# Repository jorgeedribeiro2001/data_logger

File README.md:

# Data Logger Project

## Overview
This repository contains the implementation of a data logger project designed for real-time and remote data acquisition during the shipment of products. The project includes scripts for data processing, device software, and a web interface for data visualization and control.

## Repository Structure

- **Back-End Scripts**: Scripts for data processing and storage.
- **Device Software (Microcontroller)**: Code for the microcontroller used in the data logging device.
- **Django Web-Framework**: Web application framework for interfacing with the data logger.
- **Tests and Results**: Testing scripts and result logs.
- **PCB Project**: KiCad Project of the PCB for the prototype.

## Description of the Implemented Solution

The data logger system uses the ESP32-E Firebeetle 2 microcontroller as the main unit. It works with several sensors to meet the project's requirements:

- **Vibration and Impact Monitoring**: Uses the IAM-20680 accelerometer and gyroscope.
- **Environmental Monitoring**: Uses the BME680 sensor to measure temperature, humidity, and pressure. Both sensors communicate with the microcontroller using the I2C protocol.
- **Data Storage**: Uses a PMod microSD reader module, which communicates via the SPI protocol, for local data storage.
- **Mobile Communication and GPS**: Uses the Ai-Thinker A9G module for mobile network communication and GPS tracking, interfacing via the UART protocol.

Data is sent using the MQTT protocol. Back-end scripts receive this data, convert it to JSON format, and send it to the Django web framework using HTTP Post requests.

##### Django Web Platform

The Django framework manages the data and web platform, providing features such as:

- **Data Storage**: Uses an SQLite database to store user information, trip details, configurations, and data file paths.
- **Interactive Visualization**: Uses JavaScript libraries like Highcharts for graphs and Leaflet for maps to show dynamic data on the trip monitoring page.

## Data Acquisition
A prototype was made with a PCB (KiCad Project), as shown in the next picture. This solution has one I2C connector with a Groove connector for the BME680 sensor. Two more I2C connectors are used, each with a TE Connectivity 1744418-4 connector with a 2.5mm pitch. Two SPI connectors have been added. One is for the microSD module, while the other is for the CS pin linked to GPIO 35 (A3) of the ESP32. The latter connector uses the TE Connectivity 1744418-6 with a 2.5mm pitch. This lets you add or try out other sensors. The design also has extra pins for GND, 3V3, and VCC, as well as two ESP32 serial port pins and extra free GPIOs, all marked on the PCB.

### Microcontroller Program

The microcontroller program is developed using the ESP32 microcontroller and various sensors to monitor parameters such as temperature, humidity, pressure, impacts, vibration, and location. The code is structured into tasks that handle sensor readings, data storage, and communication with the web platform via MQTT.

### Key Components:
- **ESP32 Microcontroller**: Handles sensor integration and data processing.
- **Sensors**: Include BME680 for environmental data, IMU for motion data, and the Ai-Thinker A9G for location tracking and communication.
- **SD Card**: Certain SD cards are occasionally unrecognised by the device. To ascertain the functionality of an SD card, connect the device to a computer and open a serial port. During the initialisation process, the system will indicate whether the SD card is recognisable. If the card is recognised, the available memory will be displayed. ***It is crucial to format the SD card using the FAT32 file system to ensure proper operation.*** Among the tested SD cards, the Kingston CANVAS Select Plus models with capacities of 32GB and 64GB (class 10) have proven to be reliable.

- **SIM Card**: The device is configured to utilise a SIM plan card for communication via a 2G network to access the internet. The SIM operator employed in this instance is Vodafone Portugal, with the Access Point Name (APN) specified as `net2.vodafone.pt`.
   
   ***It is crucial to note that if a different SIM operator is used, it is necessary to modify the APN configuration within the hardware programme to match the new operator's APN. Furthermore, it is imperative to disable the PIN on the SIM card, as the device lacks the capability to handle PIN entry.*** This functionality must be implemented to avoid potential security vulnerabilities.

### Running the Microcontroller Program:
1. **Set Up the Development Environment**:
   - Install the necessary tools and libraries for ESP32 development.
   - Use the Arduino IDE or PlatformIO for code uploading.

2. **Upload the Code**:
   - Connect the ESP32 to your computer.
   - Compile and upload the code from the `microcontroller` directory.

For initial configurations, the device is pre-configured with specific settings, such as a unique identifier, the initial MQTT address and port, and the APN for network connectivity. This can be encounter on the PogV8.ino file.

If you do not wish to use the remote configuration feature, you can manually define each configuration below in the `Definitions of Global Variables of the Program` section. To do this, you will need to set the `remote_configuration` variable to `false`. 

In the case of remote configuration, if a configuration file is present, the system variables are set according to the specifications outlined in the JSON document created in the "Create Trip" webpage. If the internal memory does not contain a configuration file, the A9G module is activated and configured. This module subscribes to the "config" topic on the MQTT broker and awaits the receipt of the JSON file for up to 60 seconds. During this interval, the embedded LED on the microcontroller is programmed to blink at 500 ms intervals. The user must access the Devices Manager webpage and then press the button "Send Configuration."
Upon receipt of a file, the device proceeds to process it and verify whether the JSON file’s device ID matches the ID coded into the device. Each device ID is unique. If the IDs match, the device sets all global variables and copies the JSON file to the internal memory. Once the configuration is complete, the LED remains illuminated for three seconds before turning off. This signifies the setup process is finished and the system is ready for operation.

The end mode, represented in Figure 4.13, is initiated when the user presses the embedded button on the microcontroller for a period of three seconds, thereby initiating the procedure and activating the embedded LED.

## Data Processing and Visualization

The data processing and visualization for the data logger system is managed through a series of scripts and a Django-based web platform. The system architecture and the functions of each script are described below.

### System Architecture

1. **Data Acquisition**:
   - The data logger devices collect data on temperature, humidity, pressure, impacts, vibration, and location.
   - This data is transmitted to the MQTT Broker (Mosquitto) using the MQTT protocol.

2. **Data Processing**:
   - **Script Data Receiver**: Subscribes to the MQTT topics to receive data from the data loggers.
   - **Script Data Processing**: Processes the raw data, converts it into JSON format, and prepares it for storage and visualization.
   - **Script Remote Configuration**: Publishes configuration settings to the data loggers.

3. **Data Storage and Management**:
   - The processed data is stored in an SQLite database, which keeps information about users, trips, trip configurations, and data file paths.
   - Additional processing by **Script Data PSD Processing** converts the raw data for FFT segments into Power Spectral Density (PSD) format for further analysis in the web platform.

4. **Web Framework (Django)**:
   - **Views.py**: Handles HTTP requests and returns responses to the client. It interacts with the models and templates to fetch and display data.
   - **Models.py**: Defines the database schema and interacts with the SQLite database to retrieve and store data.
   - **Urls.py**: Maps URLs to the corresponding views, enabling navigation within the web application.
   - **Templates**: HTML files that render the data into user-friendly web pages.

5. **Visualization**:
   - The web platform uses JavaScript libraries such as Highcharts and Leaflet for interactive data visualization.
   - **Highcharts**: Generates interactive graphs to display real-time and historical data on environmental conditions and impacts.
   - **Leaflet**: Provides map visualizations with recorded GPS points for tracking the location of shipments.

### Process Flow

- Data is continuously collected by the data loggers and transmitted via MQTT.
- The **Script Data Receiver** listens for incoming data and passes it to the **Script Data Processing**.
- Processed data is stored in the SQLite database and can be accessed through the Django web platform.
- Users can interact with the platform to configure devices, monitor ongoing trips, and visualize data through dynamic graphs and maps.

### Running the Server

When setting up the server, three key considerations must be addressed:

- **MQTT Server Configuration**: Although it is possible to use an external MQTT server, such as broker.hivemq.com or broker.emqx.io, it is advisable to install and configure Eclipse Mosquitto on the server to ensure greater system reliability. ***Additionally, Port 1883 should be opened for public access***.

- **Script Data Receiver**: Ensure that the Script Data Receiver (Python Script) is running continuously. This script is designed to operate without interruption and includes error-handling mechanisms to facilitate automatic rebooting. ***It is important to configure the MQTT address and port at the beginning of the program.***

- **Django Web Framework Configuration**: Properly configure the Django web framework. Detailed instructions for configuring Django will be provided in the subsequent section.

#### Running the Django Web-Framework

1. **Clone the Repository**:
   ```bash
   git clone https://github.com/jorgeedribeiro2001/data_logger_project.git
   cd data_logger_project
   ```

2. **Install Dependencies**:
   - For Python components, use the requirements file:
     ```bash
     pip install -r requirements.txt
     ```

3. **Run the Django Application**:
   - Navigate to the Django project directory:
     ```bash
     cd django_project
     ```
   - Apply migrations:
     ```bash
     python manage.py migrate
     ```
   - Create a superuser to access the admin interface:
     ```bash
     python manage.py createsuperuser
     ```
   - Start the development server:
     ```bash
     python manage.py runserver
     ```
   - Access the application at `http://127.0.0.1:8000/`.

To run the Django application over the internet, ensure you have a public IP address and an available port.
It is notable that the platform was not developed for public porposes and not went with any security concerns. Follow these steps to run the application:

1. **Open the Server to External Access**:
   Run the Django development server with the following command to make it accessible over the internet:
   ```bash
   python manage.py runserver 0.0.0.0:8000
   ```

2. **Public IP and Port**:
   - Ensure your server's firewall allows traffic on the specified port (e.g., 8000).
   - Configure your router to forward incoming traffic on this port to your server if running behind a NAT.

3. **Security Considerations**:
   - This platform was developed for demonstration purposes and internal use only.
   - It lacks security features necessary for a public-facing application.
   - If you intend to make this application accessible over the internet, implement proper security measures such as HTTPS, firewalls, authentication, and regular security audits.

4. **Deployment Recommendations**:
   - For production deployment, use a robust web server like Nginx or Apache as a reverse proxy.
   - Consider using a WSGI server like Gunicorn or uWSGI to serve the Django application.
   - Set up SSL/TLS certificates for secure HTTPS connections.

### Graphical Interface

The graphical interface of the data logger system includes several user-accessible pages designed as adaptable templates. These templates ensure that the HTML pages dynamically respond to user requests. For instance, when a user monitors a trip, the page's structure and elements adjust automatically to display the specific trip data selected by the user. Below is a visual representation of the hierarchical structure of these pages:

*Figure: Web Pages Interaction Diagram*

#### Page Descriptions

##### User Login Page
The user login page is the primary access point for users. It features a straightforward interface where users can enter their credentials. Upon successful login, users are redirected to the appropriate dashboard. Administrators can also access the administrative platform from this page.

*Figure: User Login Layout*

##### Administrator Platform
This platform is accessible only to administrators. It provides comprehensive data access and user management capabilities, allowing administrators to manage users, modify values in the SQLite database, and oversee data collected by the devices.

*Figure: Administrator Platform Layout*

##### Device Manager Page
Upon logging in, users are redirected to the Device Manager page. This page can also be accessed via the menu bar. It requires user authentication and displays the devices added by the user. Administrators can view all devices. Users can see device status, end trips, configure devices remotely, and view logs.

*Figure: Device Manager Page Layout*

##### Create Trip Page
This page allows users to create a new trip and configure the associated device settings. Users can navigate to this page via the menu bar or through a specific link. They can define the trip name, select an available data logger, and set the start date. Configuration parameters can be set, and a JSON file can be generated for saving on the user's computer.

*Figure: Create Trip Page Layout*

##### Select Trip Page
The Select Trip page allows users to view and select from a list of their trips. Users can delete a trip or proceed to monitor it. This page is accessible via the menu bar and requires user authentication.

*Figure: Select Trip Page Layout*

##### Monitoring Trip Page
This page is crucial for data analysis and visualization. It is divided into sections for general trip details, BME data (temperature, humidity, pressure), IMU data (impact, vibration), and location data. Each section provides detailed analysis and interactive graphs.

*Figure: Monitoring Page: Trip Details and BME Data Sections Layout*

*Figure: Monitoring Page: IMU Data Section Layout*

*Figure: Monitoring Page: Location Section Layout*

#### JavaScript Libraries
The interactive graphs and maps are created using the Highcharts and Leaflet JavaScript libraries. Highcharts is used for generating interactive graphs, while Leaflet is used for creating interactive maps with recorded position points. These tools provide dynamic visualization of the data collected by the data logger devices.

This graphical interface ensures a user-friendly and efficient way to manage devices, create and monitor trips, and visualize data for analysis, making it a vital part of the data logger system.

## Troubleshooting

##### When I turn on the device, the light is always on indefinitely.

This issue may arise due to initialization errors, often related to inaccessible sensors or the communication module's inability to connect to the network for remote configuration or microSD incompatibility. To troubleshoot, follow these steps:

- Verify that all sensor connections are secure.
- Ensure a compatible microSD card is in place.
- Confirm that the SIM card is functioning correctly.
- Check that the MQTT settings are properly configured.
  
To determine the specific cause, connect the device to a computer, open a serial port, and restart the device. This will display initialization information on the serial port. The baud rate should be set to 115200 bps.

##### The remote configuration does not work (the light keeps blinking after I click the Send Configuration button on the web platform).

This issue may be attributed to improper configuration of the MQTT server settings. Ensure that the device is configured with the correct MQTT broker address and port. Additionally, verify that the appropriate settings have been entered on the Create Trip webpage.

##### Despite the device being deployed in the field, the web platform is not receiving or displaying updated data.

Verify if the script data receiver is running with the correct MQTT configurations. Additionally, check if the issue is isolated to a single device or affects multiple devices. Examine the last communication timestamp of the device and ensure that the trip configurations have the communication interval set correctly. If all these aspects are in order, contact the repository owner for further assistance. Remember that the device communication might be skipped during the programmed interval but will resume in the subsequent interval.

## License
This project is licensed under the GNU General Public License v3.0.

## Contact
For any queries, contact the repository owner on LinkedIn page: https://www.linkedin.com/in/jorgeedribeiro/ 

---

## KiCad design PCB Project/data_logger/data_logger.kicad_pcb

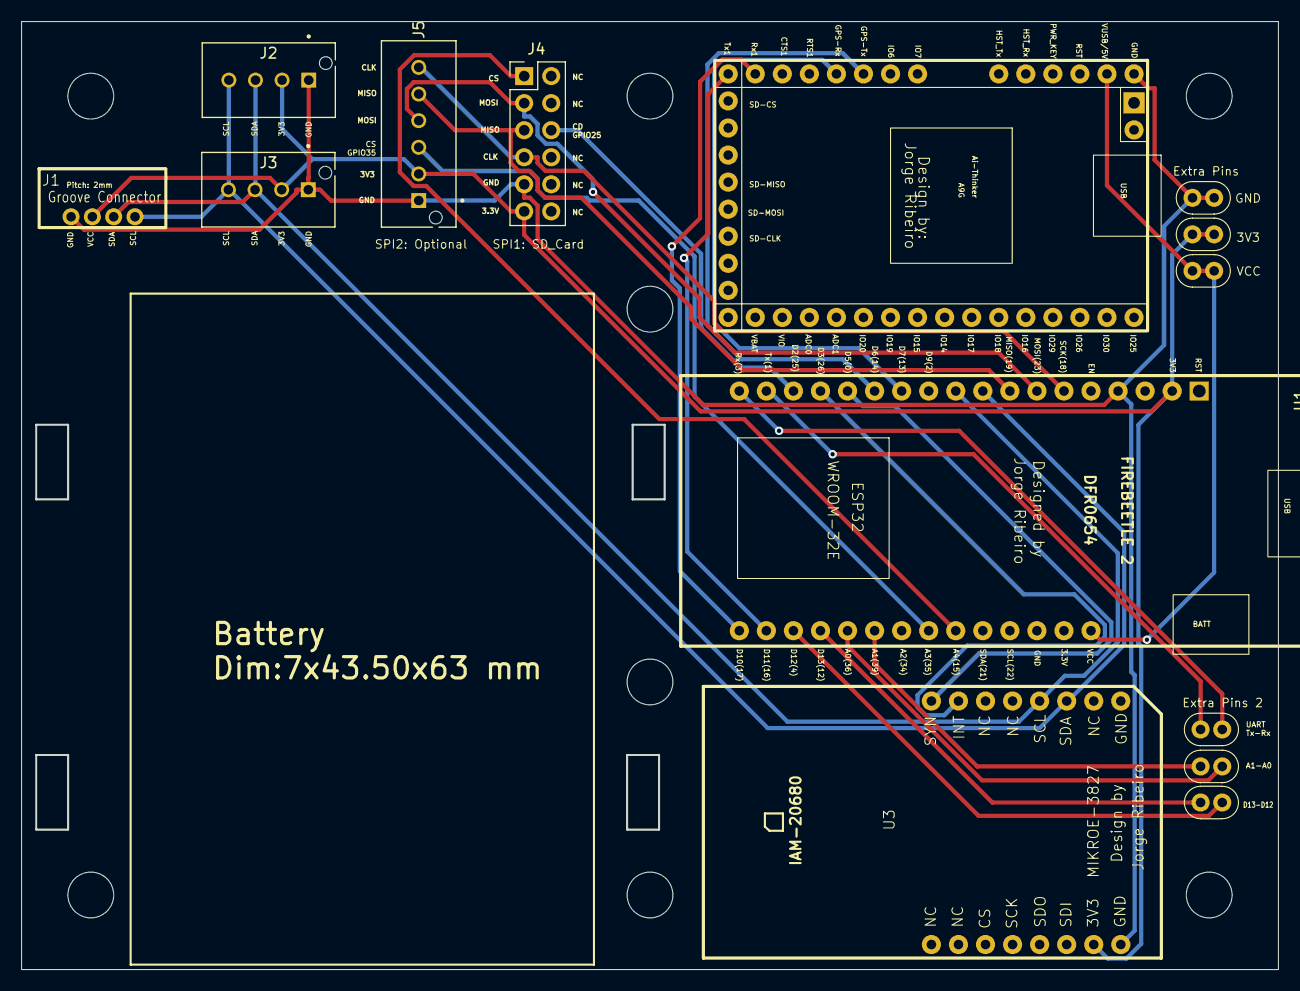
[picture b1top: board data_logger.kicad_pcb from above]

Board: 2 copper layers, 118.0 x 89.0 mm, 22 parts (0 on the bottom side), 23 nets.

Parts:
J1: GrooveConnector_1
J2, J3: TE_1744418-4
J4: SD Connector; PinHeader_2x06_P2.54mm_Vertical
J5: SPI Connector Optional; TE_1744418-6
J6, J7, J8, J9, J10, J11: Conn_01x02; extraconnectors_1x02_P2.54mm
REF1, REF2, REF3, REF4, REF5, REF6, REF7, REF8: MountingHole_4.3mm_M4
U1: MODULE_DFR0654
U2: A9G-Kit
U3: MIKROE-3827

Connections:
+3V3: J1.2 (VCC), J2.2 (VCC), J3.2 (VCC), J4.6, J5.2, J6.1, J6.2, U1.2 (3.3V), U3.7 (3V3)
+5V: J7.1, J7.2, U1.19 (VCC), U2.37 (VUSB/5V)
Earth: J1.1 (GND), J2.1 (GND), J3.1 (GND), J4.5, J5.1, J8.1, J8.2, U1.4 (GND), U2.38 (GND), U3.8 (GND)
unnamed: J1.4 (SCL), J2.4 (SCL), J3.4 (SCL), U1.9 (SCL), U3.14 (SDA)
unnamed: J1.3 (SDA), J2.3 (SDA), J3.3 (SDA), U1.10 (SDA), U3.13 (SCL)
unnamed: J4.1, U1.24 (A4)
unnamed: J4.2, J5.4, U1.7 (MOSI)
unnamed: J4.3, J5.5, U1.8 (MISO)
unnamed: J4.4, J5.6, U1.6 (SCK)
unnamed: J4.9, U1.16 (D2)
unnamed: J5.3, U1.25 (A3)
unnamed: J9.1, U1.17 (TX)
unnamed: J9.2, U1.18 (RX)
unnamed: J10.1, U1.27 (A1)
unnamed: J10.2, U1.28 (A0)
unnamed: J11.1, U1.29 (D13)
unnamed: J11.2, U1.30 (D12)
unnamed: U1.15 (D3), U3.10 (INT)
unnamed: U1.14 (D5), U3.9 (SYN)
unnamed: U1.13 (D6), U2.30 (GPS_TX)
unnamed: U1.12 (D7), U2.29 (GPS_RX)
unnamed: U1.32 (D10/UART2-Tx), U2.26 (RX1)
unnamed: U1.31 (D11/UART2-Rx), U2.25 (TX1)

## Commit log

2023-12-04 README.md
2023-12-04 A9G.ino
2024-04-09 add energy consumption tests
2024-04-11 Creating Script for Receiving Data
2024-05-24 Add the humidity test
2024-05-25 Update the tests
2024-06-03 update tests
2024-06-03 Update with hardware program and tests
2024-06-03 Add django webframework
2024-06-13 Update Tests and Results
2024-06-13 Readme update
2024-06-14 Create LICENSE
2024-06-21 Add temperature Validation Test

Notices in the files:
README.md:
This project is licensed under the GNU General Public License v3.0.
